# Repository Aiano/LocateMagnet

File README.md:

# 磁定位系统 LocateMagnet

## 简介

​	这个项目来源于一个课设，要求使用AMR磁传感器对小磁铁进行三维空间定位，定位范围1cm x 1cm x 1cm，定位精度要求达到0.1mm。

​	本项目采用了5x5 AMR磁传感器阵列，在远超课设要求的范围下，同时满足精度要求，此外还能实时检测，画出移动轨迹。

## 文件结构

- Firmware: STM32代码
- Hardware: PCB工程
- Mechanical: 测试架和磁铁胶囊的3D模型
- Result: 测试结果
- Software: MATLAB上位机代码
- Tools: WCHLINK固件、烧录器、配置器
- Render: 渲染图

## 运行环境

- Keil 5
- STM32CubeMX
- KiCAD 6
- MATLAB **2023b**

## 复刻流程

1. PCB投板：可以直接拿gerber压缩包去投板

2. 购买元件：bom文件夹里有元件清单

3. 焊接：建议使用回流焊，没有的可以用热风枪代替，建议**先焊接除传感器外的其他元件**，测试可用后，再焊接传感器。该芯片是WLP晶圆级封装，很小，可以先在焊盘上涂助焊剂，放上芯片，热风枪吹焊，同时在显微镜下观察，当芯片轻微移动归位时，用镊子轻轻推动，如果芯片被推后能够归位，说明焊接成功。

4. WCHLINK固件烧录：PCB板载一个WCHLINK，方便调试，先**短接**PCB上的**UPG焊盘**，连接PC，检测到设备后，使用**WCHISPTool**下载`WCHLINK_V02.03.bin`，然后把UPG焊盘断开，再次连接PC，初次烧录固件，WCHLINK处于RISC-V模式，打开WCH-LinkUtility，点Get获取当前Mode，切换成**WCH-LinkDAP-WINUSB**，点Set，配置好后WCHLINK会变成ARM模式，如果使用Keil能检测到stm32芯片就算成功

5. stm32固件烧录：正常使用Keil下载代码，调试器选择DAPLINK

    Optional：如果板载芯片是GD32，请安装`Tools/GigaDevice.GD32F10x_DFP.2.0.3.pack`，然后选择`..._GD32_Compatible`的Keil工程下载

6. 串口调试助手：使用DAPLINK自带的串口输出数据，如果传感器都正常，应该能读到U ··· V ··· W ···系列数据，不会有No Ack提示

7. 打印测试架： 注意测试架只能放入直径3mm的小磁铁

8. 打开`compute_NT.mlx`：串口号要改成自己的串口，逐块运行代码，先移开磁体，获得校准矩阵，然后放上磁体，填入磁铁真实位置，如果读到的是空矩阵，再运行两遍尝试，最后计算出N_T这个和磁铁磁化强度相关的常数

9. 打开`real_time.m`：注意MATLAB必须先定位到`real_time`文件夹，填入N_T常数，先移开磁体，运行，然后再放上磁铁，最开始会有点卡，连续运行就会变流畅

## 相关链接

> [Arm Keil | Devices](https://www.keil.arm.com/devices/)

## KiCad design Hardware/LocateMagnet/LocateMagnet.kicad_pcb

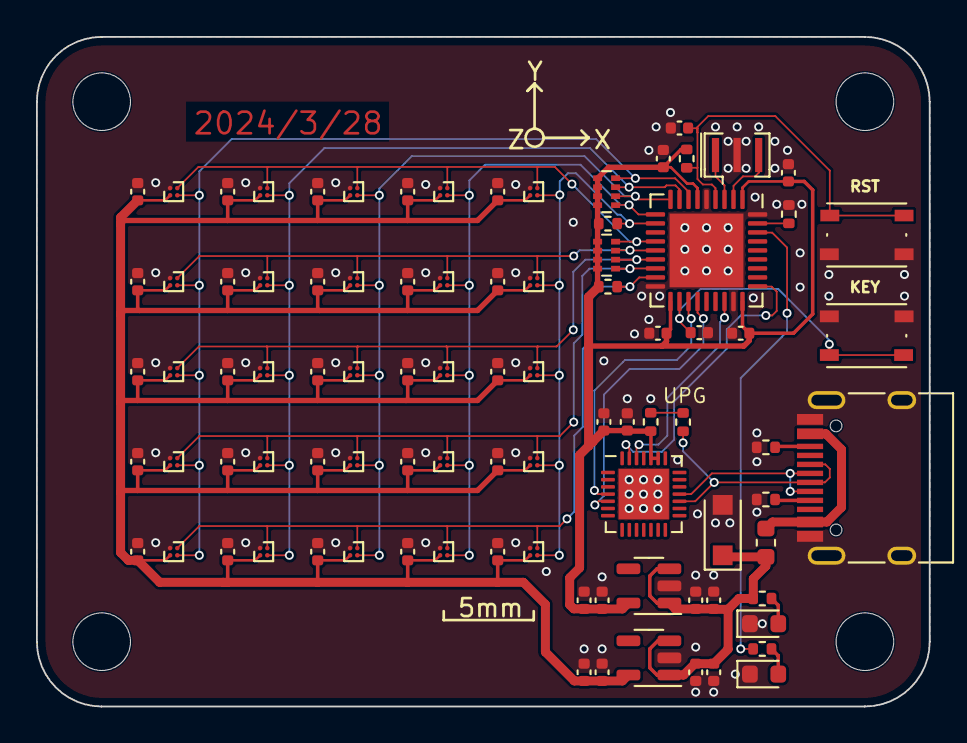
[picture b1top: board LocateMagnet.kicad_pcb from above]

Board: 2 copper layers, 49.6 x 37.2 mm, 94 parts (0 on the bottom side), 32 nets.

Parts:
C1, C2, C3, C4, C5, C6, C7, C8, C9, C10, C11, C12, C13, C14, C15, C16, C17, C18, C19, C20, C21, C22, C23, C24, C25, C26, C28, C31, C32, C34, C35, C36, C37, C38, C39, C40, C41: 0.1u; C_0402_1005Metric
C27, C29, C30, C33: 10u; C_0402_1005Metric
D1: TVS 6V; D_SOD-123F
D2: LED-GREEN; LED_0603_1608Metric
D3: LED-RED; LED_0603_1608Metric
F1: 6V1A; Fuse_0603_1608Metric
H1, H2, H3, H4: MountingHole; MountingHole_3.2mm_M3
J2: USB_C_Receptacle_USB2.0; USB_C_Receptacle_HRO_TYPE-C-31-M-12
R1, R2, R3, R4, R5: 10K; R_0402_1005Metric
R6, R7: 5.1k; R_0402_1005Metric
R8, R9: 10k; R_0402_1005Metric
RN1, RN2: 4*10k; R_Array_Concave_4x0402
SW1: RST; SW_Push_1P1T_NO_Vertical_Wuerth_434133025816
SW2: KEY; SW_Push_1P1T_NO_Vertical_Wuerth_434133025816
TP1: TestPoint_2Pole; R_0402_1005Metric
U1, U2, U3, U4, U5, U6, U7, U8, U9, U10, U11, U12, U13, U14, U15, U16, U17, U18, U19, U20, U21, U22, U23, U24, U25: MMC5603NJ; WLP-4_0.83x0.83mm_P0.4mm
U26: CH549F; QFN-28-1EP_4x4mm_P0.4mm_EP2.8x2.8mm
U27: STM32F103TBUx; QFN-36-1EP_6x6mm_P0.5mm_EP4.1x4.1mm
U28, U29: RT9013-Lite; SOT-23-5
Y1: 3215-8MHz; Resonator_SMD_Murata_CSTxExxV-3Pin_3.0x1.1mm

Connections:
+3.3V: C1.1, C2.1, C3.1, C4.1, C5.1, C6.1, C7.1, C8.1, C9.1, C10.1, C11.1, C12.1, C13.1, C14.1, C15.1, C16.1, C17.1, C18.1, C19.1, C20.1, C21.1, C22.1, C23.1, C24.1, C25.1, C32.1, C33.1, U1.B1 (VDD), U2.B1 (VDD), U3.B1 (VDD), U4.B1 (VDD), U5.B1 (VDD), U6.B1 (VDD), U7.B1 (VDD), U8.B1 (VDD), U9.B1 (VDD), U10.B1 (VDD), U11.B1 (VDD), U12.B1 (VDD), U13.B1 (VDD), U14.B1 (VDD), U15.B1 (VDD), U16.B1 (VDD), U17.B1 (VDD), U18.B1 (VDD), U19.B1 (VDD), U20.B1 (VDD), U21.B1 (VDD), U22.B1 (VDD), U23.B1 (VDD), U24.B1 (VDD), U25.B1 (VDD), U29.5 (VOUT)
+3V3: C28.1, C29.1, C34.1, C35.1, C36.1, C37.1, C38.1, C39.1, R1.2, R2.2, R4.2, R5.2, RN1.1 (R1.1), RN1.2 (R2.1), RN1.3 (R3.1), RN1.4 (R4.1), RN2.1 (R1.1), RN2.2 (R2.1), RN2.3 (R3.1), RN2.4 (R4.1), U26.23 (VDD), U26.24 (V33), U27.1 (VDD), U27.6 (VDDA), U27.19 (VDD), U27.27 (VDD), U28.5 (VOUT)
+5V: C26.1, C27.1, C30.1, C31.1, D1.1 (K), F1.2, R9.1, U28.1 (VIN), U28.3 (EN), U29.1 (VIN), U29.3 (EN)
/DAP_RX: U26.4 (P3.0/RXD), U27.21 (PA9)
/DAP_TX: U26.5 (P3.1/TXD), U27.22 (PA10)
/KEY: C41.1, SW2.2, U27.20 (PA8)
/MCU_LED: R8.1, U27.34 (PB7)
/NRST: C40.1, R2.1, SW1.2, U27.4 (NRST)
/SWCLK: U26.27 (P1.4/SCS/UCC1/AIN4), U27.28 (PA14)
/SWDIO: U26.26 (P1.1/T2EX/CAP2/AIN1), U27.25 (PA13)
/USB_DM: J2.A7 (D-), J2.B7 (D-), U26.18 (P5.0/DM/UDM)
/USB_DP: J2.A6 (D+), J2.B6 (D+), TP1.1, U26.17 (P5.1/DP/UDP)
GND: C1.2, C2.2, C3.2, C4.2, C5.2, C6.2, C7.2, C8.2, C9.2, C10.2, C11.2, C12.2, C13.2, C14.2, C15.2, C16.2, C17.2, C18.2, C19.2, C20.2, C21.2, C22.2, C23.2, C24.2, C25.2, C26.2, C27.2, C28.2, C29.2, C30.2, C31.2, C32.2, C33.2, C34.2, C35.2, C36.2, C37.2, C38.2, C39.2, C40.2, C41.2, D1.2 (A), D2.1 (K), D3.1 (K), J2.A1 (GND), J2.A12 (GND), J2.B1 (GND), J2.B12 (GND), J2.S1 (SHIELD), R3.2, R6.2, R7.2, SW1.1, SW2.1, U1.A1 (VSA), U2.A1 (VSA), U3.A1 (VSA), U4.A1 (VSA), U5.A1 (VSA), U6.A1 (VSA), U7.A1 (VSA), U8.A1 (VSA), U9.A1 (VSA), U10.A1 (VSA), U11.A1 (VSA), U12.A1 (VSA), U13.A1 (VSA), U14.A1 (VSA), U15.A1 (VSA), U16.A1 (VSA), U17.A1 (VSA), U18.A1 (VSA), U19.A1 (VSA), U20.A1 (VSA), U21.A1 (VSA), U22.A1 (VSA), U23.A1 (VSA), U24.A1 (VSA), U25.A1 (VSA), U26.29 (GND), U27.5 (VSSA), U27.18 (VSS), U27.26 (VSS), U27.36 (VSS), U27.37 (VSS), U28.2 (GND), U29.2 (GND), Y1.2
unnamed: D2.2 (A), R8.2
unnamed: D3.2 (A), R9.2
unnamed: F1.1, J2.A4 (VBUS), J2.A9 (VBUS), J2.B4 (VBUS), J2.B9 (VBUS)
unnamed: J2.A5 (CC1), R7.1
unnamed: J2.B5 (CC2), R6.1
unnamed: R1.1, TP1.2
unnamed: R3.1, U27.35 (BOOT0)
unnamed: U27.2 (PD0), Y1.3
unnamed: U27.3 (PD1), Y1.1
SCL1: RN2.8 (R1.2), U1.A2 (SCL), U2.A2 (SCL), U3.A2 (SCL), U4.A2 (SCL), U5.A2 (SCL), U27.13 (PA6)
SCL2: RN2.7 (R2.2), U6.A2 (SCL), U7.A2 (SCL), U8.A2 (SCL), U9.A2 (SCL), U10.A2 (SCL), U27.14 (PA7)
SCL3: RN2.6 (R3.2), U11.A2 (SCL), U12.A2 (SCL), U13.A2 (SCL), U14.A2 (SCL), U15.A2 (SCL), U27.15 (PB0)
SCL4: RN2.5 (R4.2), U16.A2 (SCL), U17.A2 (SCL), U18.A2 (SCL), U19.A2 (SCL), U20.A2 (SCL), U27.16 (PB1)
SCL5: R5.1, U21.A2 (SCL), U22.A2 (SCL), U23.A2 (SCL), U24.A2 (SCL), U25.A2 (SCL), U27.17 (PB2)
SDA1: RN1.8 (R1.2), U1.B2 (SDA), U6.B2 (SDA), U11.B2 (SDA), U16.B2 (SDA), U21.B2 (SDA), U27.7 (PA0)
SDA2: RN1.7 (R2.2), U2.B2 (SDA), U7.B2 (SDA), U12.B2 (SDA), U17.B2 (SDA), U22.B2 (SDA), U27.8 (PA1)
SDA3: RN1.6 (R3.2), U3.B2 (SDA), U8.B2 (SDA), U13.B2 (SDA), U18.B2 (SDA), U23.B2 (SDA), U27.9 (PA2)
SDA4: RN1.5 (R4.2), U4.B2 (SDA), U9.B2 (SDA), U14.B2 (SDA), U19.B2 (SDA), U24.B2 (SDA), U27.10 (PA3)
SDA5: R4.1, U5.B2 (SDA), U10.B2 (SDA), U15.B2 (SDA), U20.B2 (SDA), U25.B2 (SDA), U27.11 (PA4)

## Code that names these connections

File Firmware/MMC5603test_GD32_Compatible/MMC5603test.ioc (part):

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Mcu.Name=STM32F103T(8-B)Ux
Mcu.Package=VFQFPN36
Mcu.UserName=STM32F103TBUx
PA0-WKUP.GPIOParameters=GPIO_Speed,PinState,GPIO_PuPd,GPIO_ModeDefaultOutputPP
PA0-WKUP.GPIO_ModeDefaultOutputPP=GPIO_MODE_OUTPUT_OD
PA0-WKUP.GPIO_PuPd=GPIO_NOPULL
PA0-WKUP.GPIO_Speed=GPIO_SPEED_FREQ_HIGH
PA0-WKUP.PinState=GPIO_PIN_SET
PA0-WKUP.Signal=GPIO_Output
PA1.GPIOParameters=GPIO_Speed,PinState,GPIO_PuPd,GPIO_ModeDefaultOutputPP
PA1.GPIO_ModeDefaultOutputPP=GPIO_MODE_OUTPUT_OD
PA1.GPIO_PuPd=GPIO_NOPULL
PA1.GPIO_Speed=GPIO_SPEED_FREQ_HIGH
PA1.PinState=GPIO_PIN_SET
PA1.Signal=GPIO_Output
PA10.GPIOParameters=GPIO_PuPd
PA10.GPIO_PuPd=GPIO_PULLUP
PA10.Mode=Asynchronous
PA10.Signal=USART1_RX
PA13.Mode=Serial_Wire
PA13.Signal=SYS_JTMS-SWDIO
PA14.Mode=Serial_Wire
PA14.Signal=SYS_JTCK-SWCLK
PA2.GPIOParameters=GPIO_Speed,PinState,GPIO_PuPd,GPIO_ModeDefaultOutputPP
PA2.GPIO_ModeDefaultOutputPP=GPIO_MODE_OUTPUT_OD
PA2.GPIO_PuPd=GPIO_NOPULL
PA2.GPIO_Speed=GPIO_SPEED_FREQ_HIGH
PA2.PinState=GPIO_PIN_SET
PA2.Signal=GPIO_Output
PA3.GPIOParameters=GPIO_Speed,PinState,GPIO_PuPd,GPIO_ModeDefaultOutputPP
PA3.GPIO_ModeDefaultOutputPP=GPIO_MODE_OUTPUT_OD
PA3.GPIO_PuPd=GPIO_NOPULL
PA3.GPIO_Speed=GPIO_SPEED_FREQ_HIGH
PA3.PinState=GPIO_PIN_SET
PA3.Signal=GPIO_Output
PA4.GPIOParameters=GPIO_Speed,PinState,GPIO_PuPd,GPIO_ModeDefaultOutputPP
PA4.GPIO_ModeDefaultOutputPP=GPIO_MODE_OUTPUT_OD
PA4.GPIO_PuPd=GPIO_NOPULL
PA4.GPIO_Speed=GPIO_SPEED_FREQ_HIGH
PA4.PinState=GPIO_PIN_SET
PA4.Signal=GPIO_Output
PA6.GPIOParameters=GPIO_Speed,PinState,GPIO_PuPd,GPIO_ModeDefaultOutputPP
PA6.GPIO_ModeDefaultOutputPP=GPIO_MODE_OUTPUT_OD
PA6.GPIO_PuPd=GPIO_NOPULL
PA6.GPIO_Speed=GPIO_SPEED_FREQ_HIGH
PA6.PinState=GPIO_PIN_SET
PA6.Signal=GPIO_Output
PA7.GPIOParameters=GPIO_Speed,PinState,GPIO_PuPd,GPIO_ModeDefaultOutputPP
PA7.GPIO_ModeDefaultOutputPP=GPIO_MODE_OUTPUT_OD
PA7.GPIO_PuPd=GPIO_NOPULL
PA7.GPIO_Speed=GPIO_SPEED_FREQ_HIGH
PA7.PinState=GPIO_PIN_SET
PA7.Signal=GPIO_Output
PA9.Mode=Asynchronous
PA9.Signal=USART1_TX
PB0.GPIOParameters=GPIO_Speed,PinState,GPIO_PuPd,GPIO_ModeDefaultOutputPP
PB0.GPIO_ModeDefaultOutputPP=GPIO_MODE_OUTPUT_OD
PB0.GPIO_PuPd=GPIO_NOPULL
PB0.GPIO_Speed=GPIO_SPEED_FREQ_HIGH
PB0.PinState=GPIO_PIN_SET
PB0.Signal=GPIO_Output
PB1.GPIOParameters=GPIO_Speed,PinState,GPIO_PuPd,GPIO_ModeDefaultOutputPP
PB1.GPIO_ModeDefaultOutputPP=GPIO_MODE_OUTPUT_OD
PB1.GPIO_PuPd=GPIO_NOPULL
PB1.GPIO_Speed=GPIO_SPEED_FREQ_HIGH
PB1.PinState=GPIO_PIN_SET
PB1.Signal=GPIO_Output
PB2.GPIOParameters=GPIO_Speed,PinState,GPIO_PuPd,GPIO_ModeDefaultOutputPP
PB2.GPIO_ModeDefaultOutputPP=GPIO_MODE_OUTPUT_OD
PB2.GPIO_PuPd=GPIO_NOPULL
PB2.GPIO_Speed=GPIO_SPEED_FREQ_HIGH
PB2.PinState=GPIO_PIN_SET
PB2.Signal=GPIO_Output
PB6.GPIOParameters=GPIO_PuPd,GPIO_Mode
PB6.GPIO_Mode=GPIO_MODE_INPUT
PB6.GPIO_PuPd=GPIO_PULLUP
PB6.Signal=GPIO_Input
PB7.GPIOParameters=GPIO_Speed,GPIO_Label
PB7.GPIO_Label=LED
PB7.GPIO_Speed=GPIO_SPEED_FREQ_HIGH
PB7.Signal=GPIO_Output
PD0-OSC_IN.Mode=HSE-External-Oscillator
PD0-OSC_IN.Signal=RCC_OSC_IN
PD1-OSC_OUT.Mode=HSE-External-Oscillator
PD1-OSC_OUT.Signal=RCC_OSC_OUT
RCC.SYSCLKFreq_VALUE=72000000
RCC.SYSCLKSource=RCC_SYSCLKSOURCE_PLLCLK
board=custom

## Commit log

2024-04-14 PCB new layout
2024-04-14 edit README.md
2024-04-14 add pictures in README.md
2024-04-14 fix picture bug
2024-04-14 add new picture
2024-05-07 add paper
2024-05-21 faster
